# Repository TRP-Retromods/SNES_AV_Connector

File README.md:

# SNES_A/V_Connector
This is another version for a SNES AV connector. This one is shorter and can be used as a drop replacement for the orginal socket one.

* PCB must be 1.6mm, Hardgold and beveled edges
* A M2.5x10mm screw is needed for holding the PCB in the housing.
* 3DPrinting must be mechanical resistant enought (like ABS or PETG)

# Links 3D parts if you don't have a printer:
* Shapeway:
Socket: http://shpws.me/RnLp
Front Panel: http://shpws.me/RnLr

* Thingiverse:
https://www.thingiverse.com/thing:3788601

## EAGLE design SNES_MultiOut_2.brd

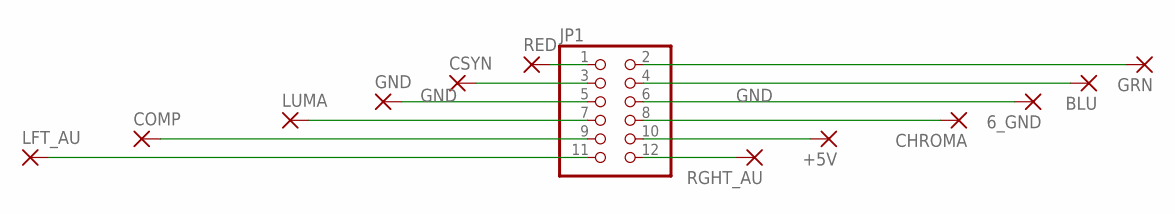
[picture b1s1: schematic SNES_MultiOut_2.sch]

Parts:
6_GND: SMD2; SMD1,27-2,54
+5V: SMD2; SMD1,27-2,54
BLU: SMD2; SMD1,27-2,54
CHROMA: SMD2; SMD1,27-2,54
COMP: SMD2; SMD1,27-2,54
CSYN: SMD2; SMD1,27-2,54
GND: SMD2; SMD1,27-2,54
GRN: SMD2; SMD1,27-2,54
JP1: PINHD-2X06_2.54; 2X06
LFT_AU: SMD2; SMD1,27-2,54
LUMA: SMD2; SMD1,27-2,54
RED: SMD2; SMD1,27-2,54
RGHT_AU: SMD2; SMD1,27-2,54

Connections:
+5V: +5V.1, JP1.10
AUDIO_LEFT: JP1.11, LFT_AU.1
AUDIO_RIGHT: JP1.12, RGHT_AU.1
BLUE: BLU.1, JP1.4
CHROMA: CHROMA.1, JP1.8
COMPOSITE: COMP.1, JP1.9
CSYNC: CSYN.1, JP1.3
GND: 6_GND.1, GND.1, JP1.5, JP1.6
GREEN: GRN.1, JP1.2
LUMA: JP1.7, LUMA.1
RED: JP1.1, RED.1

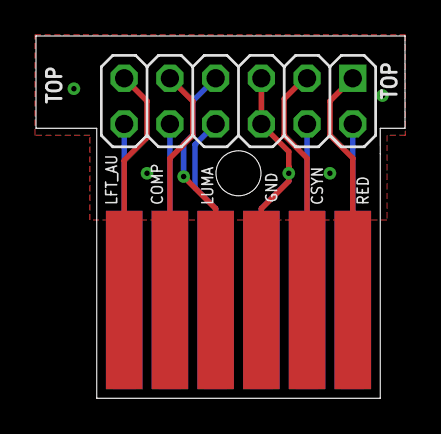
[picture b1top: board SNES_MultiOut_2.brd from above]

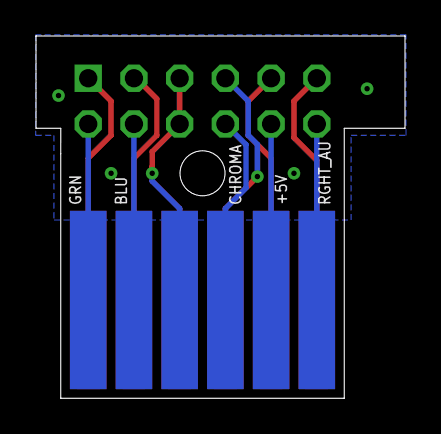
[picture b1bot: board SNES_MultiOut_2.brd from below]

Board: 2 copper layers, 20.5 x 20.1 mm, 13 parts (6 on the bottom side), 11 nets.

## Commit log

2019-08-04 Add files via upload
    Adding:
    - Adding DXF file,
    - Adding Gerber Files,
    - Adding Eagle Files,
    - Adding STL files for Socket and Front Panel
